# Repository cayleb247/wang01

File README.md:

# Wang01
Hey! My name is Caleb Wang, and I present to you the Wang01: my first macropad where I created the pcb, case, and firmware associated with the pad. I would like to thank [Hack Club](https://github.com/hackclub) for their support through their "You Ship, We Ship" program - [Hack Pad](https://github.com/hackclub/hackpad/tree/main).

#BOM:
- 1x Seeed XIAO RP2040 (through-hole)
- 1x EC11 Encoder
- 1x PCB
- 16x MX-Style switches - Gateron Milky Yellows
- 16x 1N4148 Diodes (through hole)
- 16x Blank DSA keycaps

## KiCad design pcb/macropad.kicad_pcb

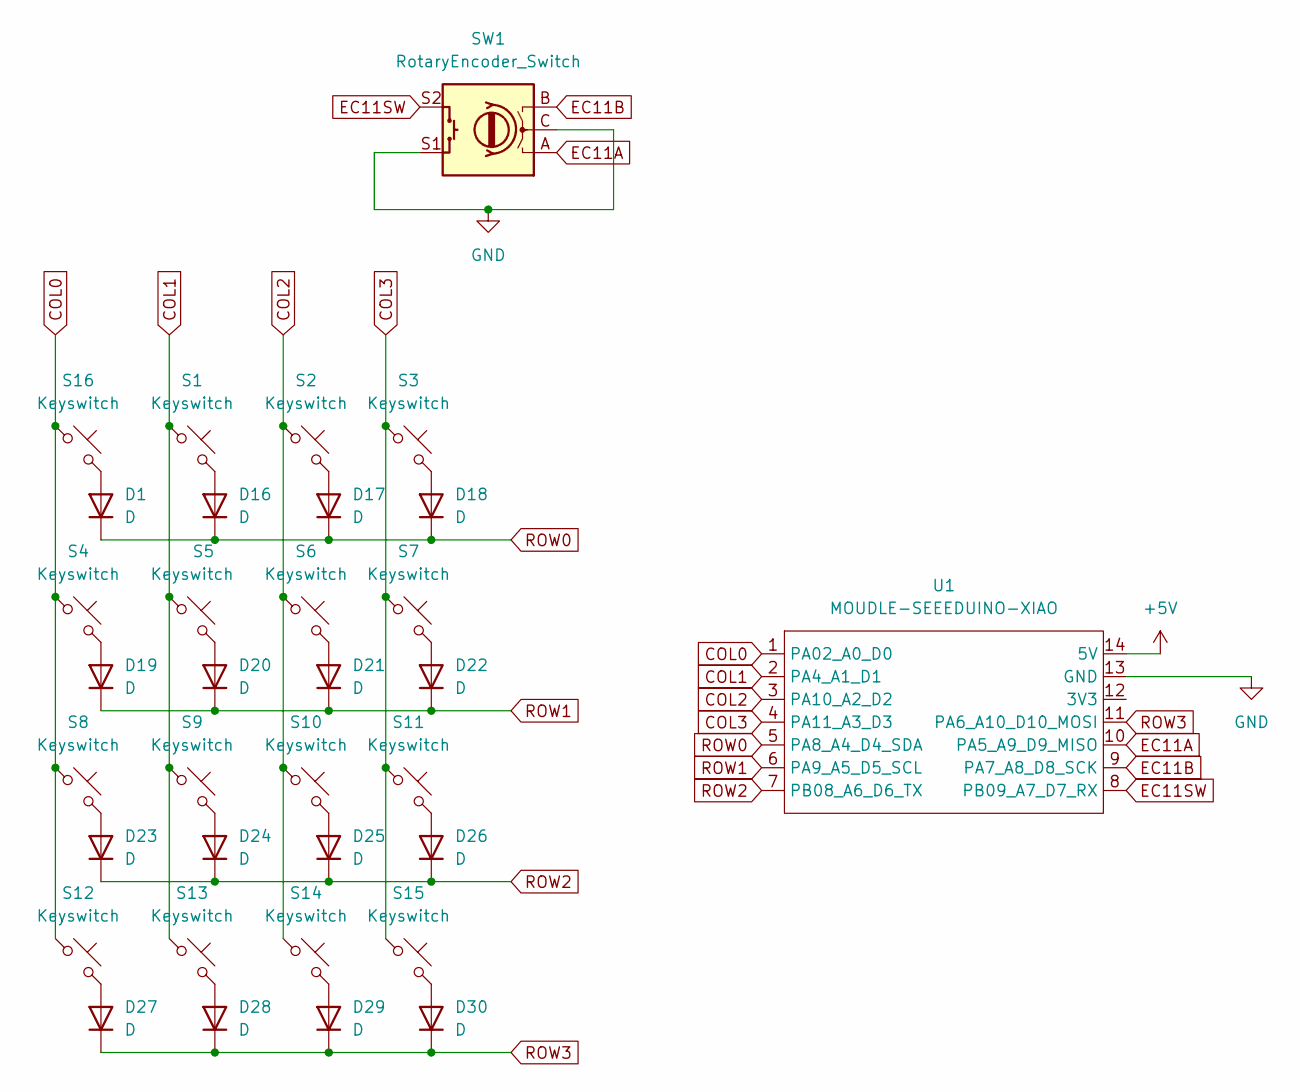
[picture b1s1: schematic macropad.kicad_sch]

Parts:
D1, D16, D17, D18, D19, D20, D21, D22, D23, D24, D25, D26, D27, D28, D29, D30: D; Diode_DO-35
S1, S2, S3, S4, S5, S6, S7, S8, S9, S10, S11, S12, S13, S14, S15, S16: Keyswitch; MX-Solderable-1U
SW1: RotaryEncoder_Switch; RotaryEncoder_Alps_EC11E-Switch_Vertical_H20mm
U1: MOUDLE-SEEEDUINO-XIAO; MOUDLE14P-2.54-21X17.8MM

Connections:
+5V: U1.14 (5V)
COL0: S4.1, S8.1, S12.1, S16.1, U1.1 (PA02_A0_D0)
COL1: S1.1, S5.1, S9.1, S13.1, U1.2 (PA4_A1_D1)
COL2: S2.1, S6.1, S10.1, S14.1, U1.3 (PA10_A2_D2)
COL3: S3.1, S7.1, S11.1, S15.1, U1.4 (PA11_A3_D3)
EC11A: SW1.A, U1.10 (PA5_A9_D9_MISO)
EC11B: SW1.B, U1.9 (PA7_A8_D8_SCK)
EC11SW: SW1.S2, U1.8 (PB09_A7_D7_RX)
GND: SW1.C, SW1.S1, U1.13 (GND)
unnamed: D1.2 (A), S16.2
unnamed: D16.2 (A), S1.2
unnamed: D17.2 (A), S2.2
unnamed: D18.2 (A), S3.2
unnamed: D19.2 (A), S4.2
unnamed: D20.2 (A), S5.2
unnamed: D21.2 (A), S6.2
unnamed: D22.2 (A), S7.2
unnamed: D23.2 (A), S8.2
unnamed: D24.2 (A), S9.2
unnamed: D25.2 (A), S10.2
unnamed: D26.2 (A), S11.2
unnamed: D27.2 (A), S12.2
unnamed: D28.2 (A), S13.2
unnamed: D29.2 (A), S14.2
unnamed: D30.2 (A), S15.2
ROW0: D1.1 (K), D16.1 (K), D17.1 (K), D18.1 (K), U1.5 (PA8_A4_D4_SDA)
ROW1: D19.1 (K), D20.1 (K), D21.1 (K), D22.1 (K), U1.6 (PA9_A5_D5_SCL)
ROW2: D23.1 (K), D24.1 (K), D25.1 (K), D26.1 (K), U1.7 (PB08_A6_D6_TX)
ROW3: D27.1 (K), D28.1 (K), D29.1 (K), D30.1 (K), U1.11 (PA6_A10_D10_MOSI)

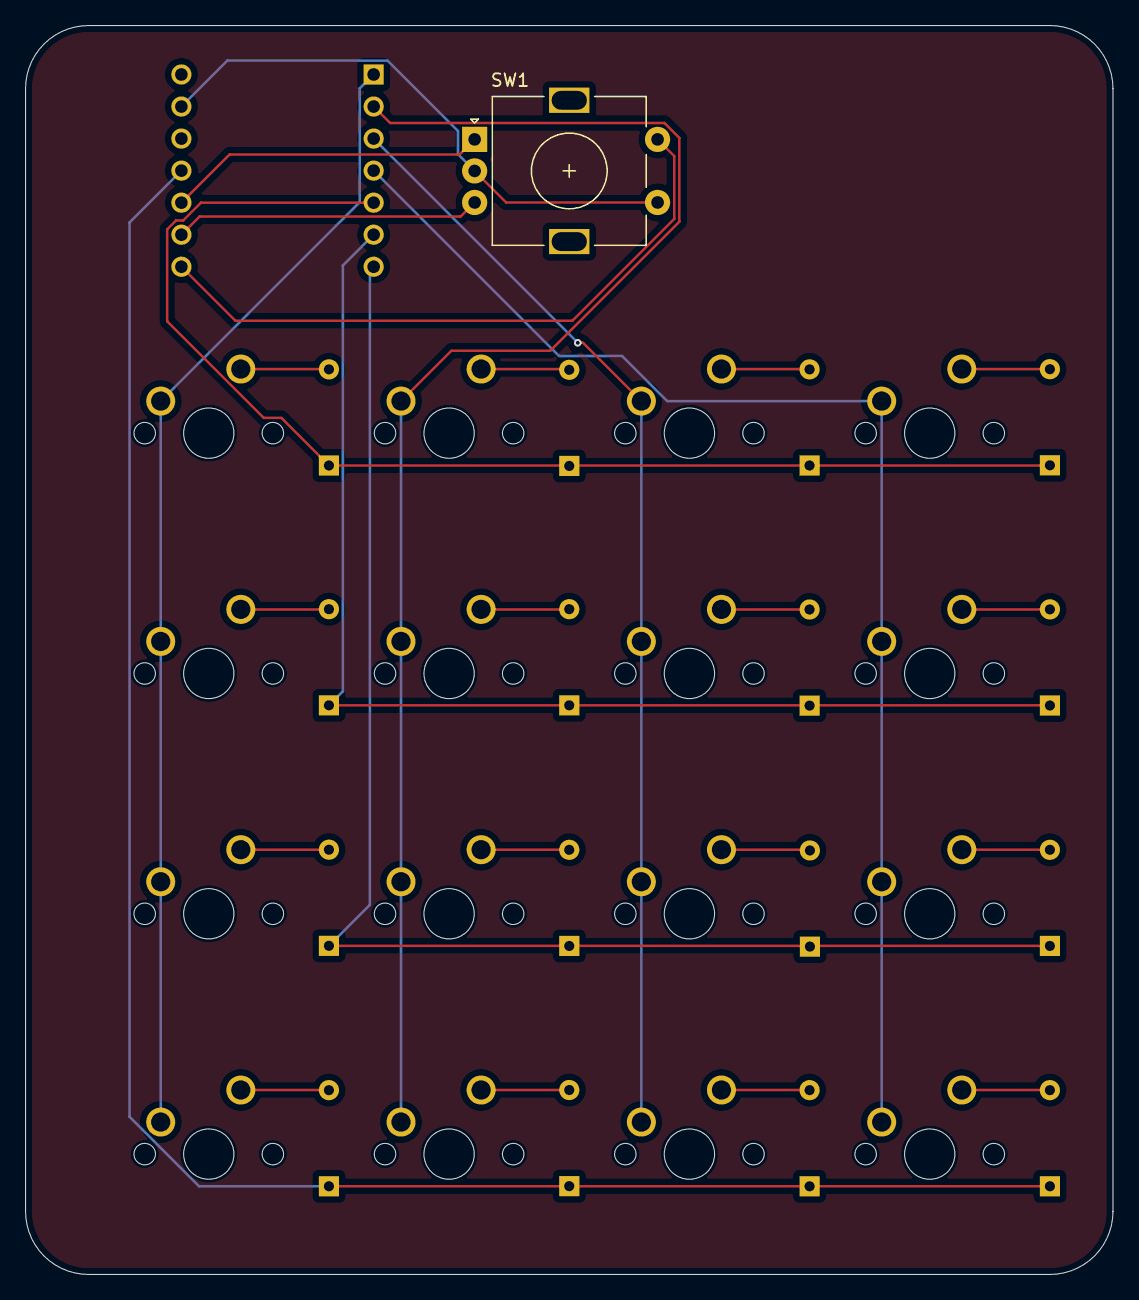
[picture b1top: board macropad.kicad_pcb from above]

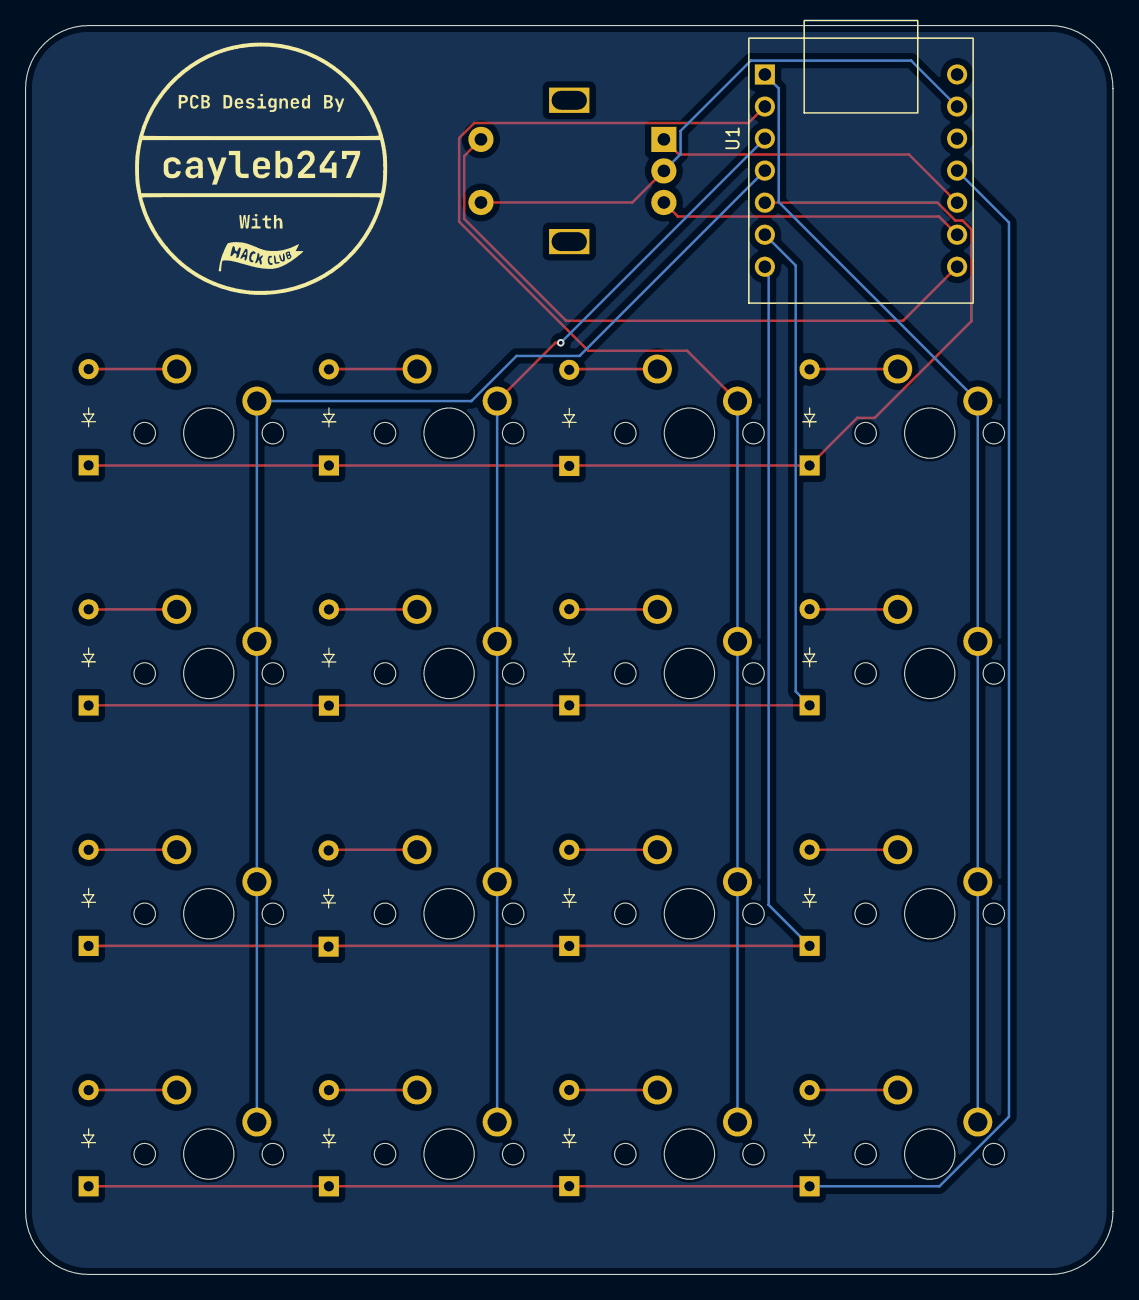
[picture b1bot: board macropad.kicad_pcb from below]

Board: 2 copper layers, 86.2 x 99.0 mm, 34 parts (17 on the bottom side), 28 nets.

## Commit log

2024-09-23 Initialize Project
2024-09-23 Add submodules
2024-09-23 Add OPL_Kicad_Library
2024-09-23 Make switches and rotary encoder
    Got a rotary encoder switch and hooked it up to the MCU
    Imported Joe Scotto's symbols and footprints for switches
    Assigned footprint for diodes
2024-09-24 Create PCB file
    Arranged components
    Routed components
    Outlined the PCB
    Made filled zones
2024-09-24 Make cutout and holes
2024-09-24 Add graphics and redo filled zones
    Additionally edge cuts were redone to correct mistake with the MCU's position relative to the PCB
2024-09-25 Resize edges of PCB and add models
2024-09-25 Rewire PCB with MCU on back
    Also centered the rotary encoder swtich
2024-09-30 Remove screw holes
2024-10-06 Make Firmware and Organization Changes
    Wrote macro pad's firmware in QMK
    Organized files by sorting them into pcb, cad, and firmware folders
    Deleted unneeded files and folders
2024-10-06 Update README.md
    "BOM:" heading was missing a space between the hashtag.
2024-10-06 Move kiCad save files into pcb folder
2024-10-06 Copy over firmware files
2024-10-06 Move macropad-backups into pcb folder
2024-10-11 Upload CAD photo
2024-10-20 Update config.h with correct encoder pins
2024-10-20 Update keyboard.json with new column
2025-03-23 Add VIA firmware
